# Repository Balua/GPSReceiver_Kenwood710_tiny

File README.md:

GPSReceiver_Kenwood710_tiny
===========================

##GPS Receiver for Kenwood D710 - Transforms the GPS Signal into the voltage level required by the Kenwood D710.

### Features

- Input lipo battery
- Voltage Regulator from V_IN to 3.3V (GPS)
- Voltage Regulator from V_IN to 5V (MAX232)
- UBlox MAX7 GPS breakout board from AVA Supplies
- Standard through hole MAX232 with electrolitic capacitors

### PCB

- All through hole components.
- Single layer for easy prototyping -> Etching.
- Voltage Regulators standing up.

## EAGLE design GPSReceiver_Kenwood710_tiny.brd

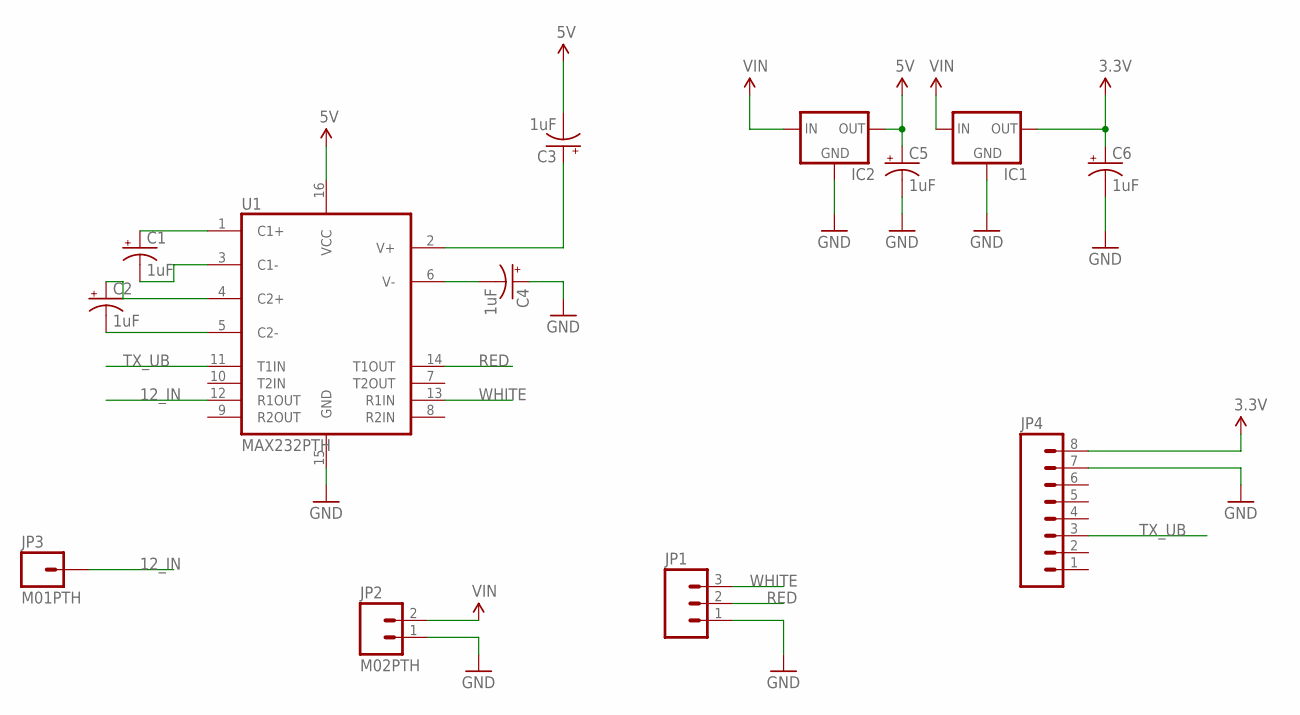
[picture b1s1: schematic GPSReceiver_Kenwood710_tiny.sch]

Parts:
C1, C2, C3, C4, C5, C6: 1uF; CPOL-RADIAL-10UF-25V
IC1, IC2: V_REG_78XX-TO-220; TO-220-ALT
JP1: M03PTH; 1X03
JP2: M02PTH; 1X02
JP3: M01PTH; 1X01
JP4: M08LOCK; 1X08_LOCK
U1: MAX232PTH; DIL16

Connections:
3.3V: C6.1 (+), IC1.OUT, JP4.8
5V: C3.2 (-), C5.1 (+), IC2.OUT, U1.16 (VCC)
12_IN: JP3.1, U1.12 (R1OUT)
GND: C4.1 (+), C5.2 (-), C6.2 (-), IC1.GND, IC2.GND, JP1.1, JP2.1, JP4.7, U1.15 (GND)
unnamed: C1.1 (+), U1.1 (C1+)
unnamed: C1.2 (-), U1.3 (C1-)
unnamed: C2.1 (+), U1.4 (C2+)
unnamed: C2.2 (-), U1.5 (C2-)
unnamed: C3.1 (+), U1.2 (V+)
unnamed: C4.2 (-), U1.6 (V-)
RED: JP1.2, U1.14 (T1OUT)
TX_UB: JP4.3, U1.11 (T1IN)
VIN: IC1.IN, IC2.IN, JP2.2
WHITE: JP1.3, U1.13 (R1IN)

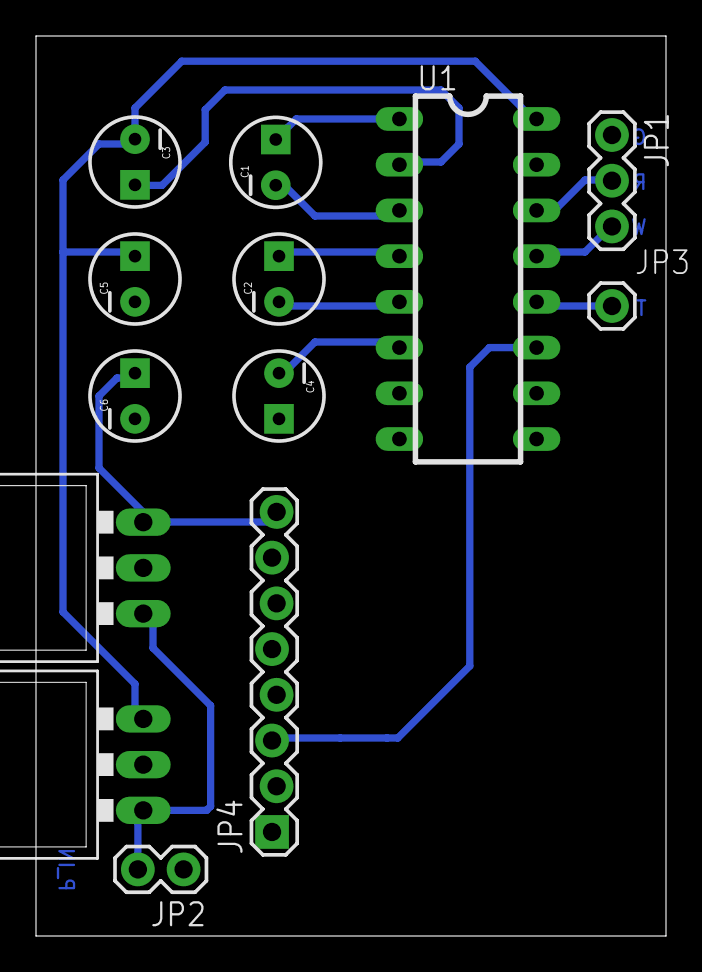
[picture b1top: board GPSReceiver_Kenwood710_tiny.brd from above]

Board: 2 copper layers, 35.0 x 50.0 mm, 13 parts (0 on the bottom side), 14 nets.

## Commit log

2014-09-17 :confetti_ball: Added .gitattributes & .gitignore files
2014-09-17 GPS Receiver for Kenwood D710
    Single Layer PCB for easy etching (smaller pcb)
2014-09-17 more clearence
    more clearence

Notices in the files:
parts and their libraries:
SparkFun-DigitalIC: Licensing: CC v3.0 Share-Alike You are welcome to use this library for commercial purposes.
